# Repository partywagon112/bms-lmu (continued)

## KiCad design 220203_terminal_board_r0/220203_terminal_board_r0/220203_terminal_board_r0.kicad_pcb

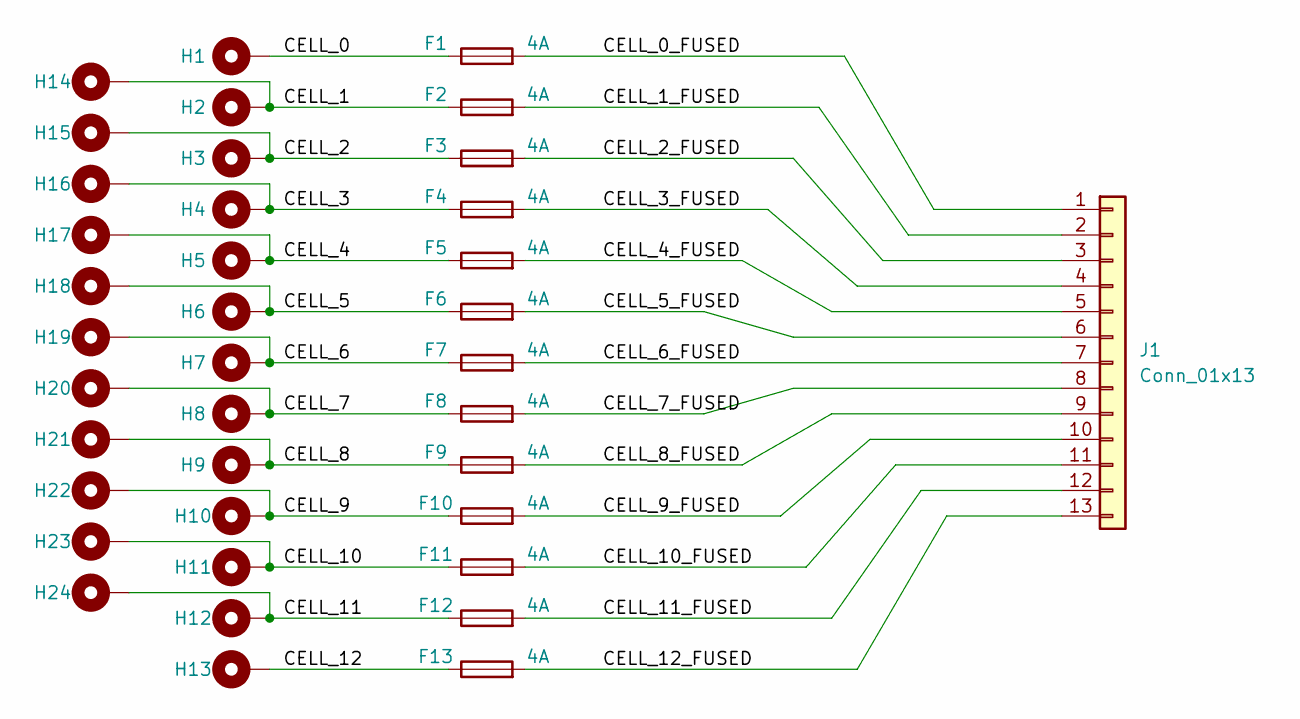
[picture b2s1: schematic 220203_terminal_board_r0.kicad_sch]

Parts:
F1, F2, F3, F4, F5, F6, F7, F8, F9, F10, F11, F12, F13: 4A; Fuse_0805_2012Metric_Pad1.15x1.40mm_HandSolder
H1, H2, H3, H4, H5, H6, H7, H8, H9, H10, H11, H12, H13, H14, H15, H16, H17, H18, H19, H20, H21, H22, H23, H24: MountingHole_Pad; MountingHole_4.3mm_M4_Pad_Via
J1: Conn_01x13

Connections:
/CELL_0: F1.1, H1.1
/CELL_0_FUSED: F1.2, J1.1
/CELL_1: F2.1, H2.1, H14.1
/CELL_1_FUSED: F2.2, J1.2
/CELL_2: F3.1, H3.1, H15.1
/CELL_2_FUSED: F3.2, J1.3
/CELL_3: F4.1, H4.1, H16.1
/CELL_3_FUSED: F4.2, J1.4
/CELL_4: F5.1, H5.1, H17.1
/CELL_4_FUSED: F5.2, J1.5
/CELL_5: F6.1, H6.1, H18.1
/CELL_5_FUSED: F6.2, J1.6
/CELL_6: F7.1, H7.1, H19.1
/CELL_6_FUSED: F7.2, J1.7
/CELL_7: F8.1, H8.1, H20.1
/CELL_7_FUSED: F8.2, J1.8
/CELL_8: F9.1, H9.1, H21.1
/CELL_8_FUSED: F9.2, J1.9
/CELL_9: F10.1, H10.1, H22.1
/CELL_9_FUSED: F10.2, J1.10
/CELL_10: F11.1, H11.1, H23.1
/CELL_10_FUSED: F11.2, J1.11
/CELL_11: F12.1, H12.1, H24.1
/CELL_11_FUSED: F12.2, J1.12
/CELL_12: F13.1, H13.1
/CELL_12_FUSED: F13.2, J1.13

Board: 2 copper layers, 37 parts (0 on the bottom side), 13 nets, no tracks yet.

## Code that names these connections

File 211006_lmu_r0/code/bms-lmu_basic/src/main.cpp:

#include <Arduino.h>
#include "bms_lmu.h"
#include "SPI.h"
#include <eXoCAN.h>
#include "TickerInterrupt.h"

/******************************************************************************
 * BMS_LMU - HARDWARE REVISION 0
 * Patrick Curtain
 * 
 * Battery Management System - Local Measurement Unit
 * 
 * An active balancer created for FYRP by Patrick Curtain and Ethan Suter, 
 * Semester 2 2021 and Semester 1 2022, at Swinburne University of Technology.
 * 
 * Code base derived from Team Swinburne FSAE
 * Available: https://github.com/Team-Swinburne/ts_20-code-development
 * 
 * Revision     Date      Comments
 * --------   --------    --------
 * 0.0        28/5/2022   Initial Code Base
 * 
 * 
******************************************************************************/

// PINOUT
#define LED0 PC13
#define CAN_TX_LED PB5
#define CAN_RX_LED PB6
#define SPI_TX_LED PB7
#define SPI_RX_LED PB8
#define FAULT_RELAY PA9
#define FAULT_RELAY_FEEDBACK PA10

// NOT SAFETY PARAMETERS
#define DISCHARGE_TIMER_LIMIT 1000
#define HEART_RATE 1000
#define CAN_INTERVAL 800
#define CANBUS_FREQUENCY 250000

#define TX_ADDRESS 0x481

// led pins
DigitalOut can_tx_led(CAN_TX_LED);
DigitalOut can_rx_led(CAN_TX_LED);
DigitalOut spi_tx_led(CAN_TX_LED);
DigitalOut spi_rx_led(CAN_TX_LED);

// Globals
Heartbeat heartbeat(FAULT_RELAY, FAULT_RELAY_FEEDBACK, LED0);
Stack stack;
PBalancer passive_balancer(stack, DISCHARGE_TIMER_LIMIT);

// Interfaces
eXoCAN can;

// Timers
TickerInterrupt ticker(TIM2, 1);

struct msg_frame
{
  uint8_t len = 8;
  uint8_t bytes[8] = {0};
};

static msg_frame	heart_frame {.len = 3},
               	bms_lower_bank {.len = 6}, 
				        bms_upper_bank {.len = 6},
               	temperature {.len = 8};

uint8_t rxData[8];

void can_tx(){
  can.transmit(TX_ADDRESS, heart_frame.bytes, heart_frame.len);
  can.transmit(TX_ADDRESS + 1, bms_lower_bank.bytes, bms_lower_bank.len);
  can.transmit(TX_ADDRESS + 2, bms_upper_bank.bytes, bms_upper_bank.len);
  can.transmit(TX_ADDRESS + 3, temperature.bytes, temperature.len);

  can_tx_led = !can_tx_led;
}

// Can receive interupt service routine
void canISR() {
	can.rxMsgLen = can.receive(can.id, can.fltIdx, can.rxData.bytes);
}


void can_rx() {
	if (can.rxMsgLen > -1) {
    can_rx_led = !can_rx_led;
	}
}

uint8_t array_to_uint8(bool arr[], int count){
    int ret = 0;
    int tmp;
    for (int i = 0; i < count; i++) {
        tmp = arr[i];
        ret |= tmp << (count - i - 1);
    }
    return ret;
}

uint16_t check_errors(){
  bool error_code[8];

	error_code[ERROR_OV_FAULT] = stack.ov_fault();
	error_code[ERROR_UV_FAULT] = stack.uv_fault();
	// error_code[ERROR_OT_FAULT] = !imd.get_IMD_ok();
	error_code[ERROR_RELAY_FAULT] = heartbeat.relay_fault();
	
	// error_code[ERROR_ORION_LOW_VOTLAGE] 	= orion.check_low_voltage();
	// error_code[ERROR_ORION_HIGH_VOLTAGE] 	= orion.check_high_voltage();
	// error_code[ERROR_ORION_OVERTEMPERATURE] = orion.check_overtemperature();
	// error_code[ERROR_PERIPHERALS] = 0;

	return array_to_uint8(error_code, 8);
}

void update_can_frames(){
  heart_frame.bytes[0] = heartbeat.state();
  heart_frame.bytes[0] = heartbeat.counter();
  heart_frame.bytes[1] = heartbeat.fault_code();

  for (int i = 0; i < 6; i++){
    bms_lower_bank.bytes[i] = stack.cell_voltage(i);
  }

  for (int i = 6; i < 12; i++){
    bms_upper_bank.bytes[i] = stack.cell_voltage(i);
  }

  // add in the temp measurement thing.
}

void state_d(){

  update_can_frames();

  switch(heartbeat.state()) {
    case (FAULT):
      // do nothing, clear the error as quickly
      // as possible.
      if (check_errors() == 0){
        heartbeat.state(IDLE);
      }
      break;
    
    case (IDLE):
      // literally do nothing!
      break;
    
    case (MEASURING):
      // stop balancing
      passive_balancer.end_balance();

      // check the passive balancer
      passive_balancer.update_stack();

      // measure the temperatures
      break;
    
    case (PASSIVE_BALANCING):
      passive_balancer.start_balance();
      break;
    
    case (ACTIVE_BALANCING):
      // not sure yet!
      break;
  }
}

void start_up_lights(){
  pinMode(PB5, OUTPUT);
  pinMode(PB6, OUTPUT);
  pinMode(PB7, OUTPUT);
  pinMode(PB8, OUTPUT);

  int scroller_time = 100;
  digitalWrite(PB5, HIGH);
  delay(scroller_time);
  digitalWrite(PB6, HIGH);
  delay(scroller_time);
  digitalWrite(PB7, HIGH);
  delay(scroller_time);
  digitalWrite(PB8, HIGH);
  delay(scroller_time);

  digitalWrite(PB5, LOW);
  delay(scroller_time);
  digitalWrite(PB6, LOW);
  delay(scroller_time);
  digitalWrite(PB7, LOW);
  delay(scroller_time);
  digitalWrite(PB8, LOW);
  delay(scroller_time);
}


// timer functions
void heartbeat_cb(){
  heartbeat.tick(check_errors());
}

void setup() {

  // start the heartbeat timer.
  start_up_lights();

  // setup the can
  can.begin(STD_ID_LEN, CANBUS_FREQUENCY, PORTA_11_12_WIRE_PULLUP);   //11 Bit Id, 500Kbps
  can.filterMask16Init(0, 0x600, 0x7ff);
  can.attachInterrupt(canISR);
  
  // setup heartbeat tickers.
  ticker.start();
  ticker.attach(heartbeat_cb, HEART_RATE);

  ticker.attach(can_tx, CAN_INTERVAL);
}

void loop() {
  // state_d();

  delay(1000);
}

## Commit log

2021-10-10 Added new a-balancer interface
2021-11-01 LMU design init
2022-01-27 Finished schematic, ready for pcb layout
2022-01-27 Changed some directories
2022-01-27 added *.ini to the .gitignore
2022-01-27 inverted logic for the LMS fault detection relay
2022-01-28 Updated BOM and footprints for non-hv components
2022-01-28 Added most footprint requirements in HV
2022-01-28 Cleaned up last components missing footprint refs
2022-01-30 Updated with Mouser links for BOM
2022-02-03 added terminal board
2022-02-03 changed to M4 terminal boards
2022-02-03 minor BOM changes
2022-02-05 Updated lmu project files to Kicad V6
    Using V6.0.1
2022-02-05 Updated lmu project with relative library paths and fixed broken symbols
2022-02-05 Updated lmu footprint lib paths, fixed most footprint errors
2022-02-13 added .ini to .gitignore
2022-02-13 fixed .gitignore
2022-02-16 Began LMU pcb layout
2022-03-16 Close to completing front side of 4-module board
2022-03-20 Installed and tested Replicate Layout plugin
    Next to do: Finalise design of singular balancing module and then start layout of large board.
    Things to update:
    - Change orientation of FETs underneath coil, add vias and copper pour on opposite side for heat dissipation
    - standardise all via stitching of all large traces to grid of small vias
    - Route last few traces
    - Ensure all traces coming of bottom side of "module" - will help with routing all traces once modules are replicated
2022-03-25 Balance module design finalised
2022-03-25 Fixed missed component in module
2022-03-25 Module replication successful
2022-03-27 Updated some components to make sourcing easier
2022-03-27 Continued layout of board sections
2022-03-29 fixed footprints for headers, started planning out zones
2022-03-30 Lots of routing and placing, according to planned layout
2022-04-05 Finishing up the power supply, starting the CAN transceiver group
2022-04-05 Fixed stuff
2022-04-06 CAN transceiver stuff almost done, still needs CAN_S finished
2022-04-13 CAN_S Finished, refining balancer module
2022-04-19 added gantt chart
2022-04-19 progress on PCB
2022-04-19 final merge before branch
2022-04-20 updated pcb still need to find j11
2022-04-20 fixed issues on higher cells, study into how to route
2022-04-20 refined in-out routing mechanism
2022-04-20 first proposal routing
2022-04-20 started layout
2022-04-20 unique traces for each tap, going towards front
2022-04-20 quick save
2022-04-20 little bit closer
2022-04-21 updated gantt chart
2022-04-23 sorted header location
2022-04-24 trying out a quick thing, recover
2022-04-25 copying layout
2022-04-25 routed upper active balancer!
2022-04-25 sorted pcb layout zones
2022-04-25 moved micro into position
2022-04-28 routed ltc3811 accessories
2022-05-01 Routed vehicle section
2022-05-03 started filling polygons
2022-05-03 finished routing - beginning cleanup and review phase
2022-05-03 Added logos
2022-05-07 silkscreen changes, shifting bun leds
2022-05-07 passes all drc checks
2022-05-07 added teardrops
2022-05-07 minor corrections, dimensioned
2022-05-07 going to bulk edit fields
2022-05-07 started to export and fix things
2022-05-07 more changes
2022-05-26 added layout presentation
2022-05-28 started code
2022-05-28 created code base for the test run
